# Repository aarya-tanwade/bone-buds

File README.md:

# BoneBuds / OSSIS

We’re building OSSIS, the first BoneBuds prototype: a Bluetooth audio system that delivers sound through bone-conduction transducers.

We have verified Bluetooth playback, wireless firmware updates and independent left/right stereo playback. Our current bench prototype uses an ESP32-WROOM-32, two MAX98357A amplifiers and two separate bone-conduction transducers (BCTs).

The next stage is moving from breadboard testing towards a compact perfboard assembly, battery-powered operation and a wearable product design.

[Current firmware](code/ossis/main/main.ino) · [Upload guide](code/README.md) · [Bench setup](docs/test-setup.md) · [Test records](docs/test-results.md) · [Development log](docs/development-log.md)

## Current status

| Test | Scope | Status |
| --- | --- | --- |
| **T01: Bluetooth A2DP playback** | Bluetooth audio reception, DSP and I²S amplification | **PASSED** · 24 October 2026 |
| **T02: Wireless OTA** | Firmware uploads over Wi-Fi using ArduinoOTA | **PASSED** · 29 October 2026 |
| **T03: Independent stereo** | Two MAX98357A amplifiers and two separate BCTs | **PASSED** |

## Audio architecture

The ESP32 receives Bluetooth Classic A2DP audio in two digital channels. Each channel passes through its own independent DSP processing chain before reaching the stereo I²S output.

Both MAX98357A amplifiers receive the shared I²S clock and data connections. Their SD_MODE configurations select different channels, allowing each amplifier to drive its own transducer.

```mermaid
flowchart TD
    phone["Phone / Bluetooth audio source"]
    bt["Bluetooth Classic A2DP"]
    esp["ESP32-WROOM-32"]

    phone --> bt
    bt --> esp

    esp --> dsp["Stereo DSP<br/>32-bit floating-point processing"]

    dsp --> left["Left DSP chain"]
    dsp --> right["Right DSP chain"]

    left --> i2s["Stereo I²S output<br/>44.1 kHz / 16-bit"]
    right --> i2s

    i2s --> bus["Shared BCLK / WS / DIN"]

    bus --> ampL["MAX98357A<br/>Left channel selected"]
    bus --> ampR["MAX98357A<br/>Right channel selected"]

    ampL --> bctL["Left BCT"]
    ampR --> bctR["Right BCT"]

    classDef source fill:#edf3f6,stroke:#7896a8,color:#17324b
    classDef processing fill:#eaf2f8,stroke:#6c91ad,color:#17324b
    classDef hardware fill:#f5f1e9,stroke:#b29b70,color:#42351e
    classDef output fill:#edf4ed,stroke:#83a286,color:#23442a

    class phone,bt source
    class esp,dsp,left,right,i2s,bus processing
    class ampL,ampR hardware
    class bctL,bctR output
```

### DSP configuration

The current stereo firmware uses separate `BoneChannelDSP` instances for left and right audio processing.

| DSP stage | Configured setting | Purpose |
| --- | --- | --- |
| Pre-gain | -4.5 dB | Creates headroom before EQ boosts |
| High-pass | 180 Hz, Q = 0.7071 | Attenuates low-frequency content |
| Peaking EQ | 2.8 kHz, +4 dB, 0.8-octave bandwidth | Emphasizes the presence region |
| High shelf | 5.5 kHz, +2.5 dB, slope = 1.0 | Adjusts high-frequency balance |
| Output limiter | Soft-knee above 90% full scale | Reduces harsh peak clipping |
| Master volume | 1.0 | Output scaling |

The DSP chain uses 32-bit floating-point calculations, followed by a soft-knee limiter and a signed 16-bit safety clamp.

The configured I²S format is **44.1 kHz, 16-bit, two channels**. Hardware APLL is enabled in the current firmware.

[Current DSP implementation](code/ossis/main/main.ino) · [T03 test documentation](code/ossis/tests/T03_independent_stereo/README.md)

## T01: Bluetooth A2DP playback

**PASSED · 24 October 2026.** We verified Bluetooth Classic A2DP streaming through the ESP32-WROOM-32, MAX98357A and one bone-conduction transducer.

[Verified T01 sketch](code/ossis/tests/T01_wroom_bt_a2dp/T01_wroom_bt_a2dp.ino) · [Reproduce the test](code/ossis/tests/T01_wroom_bt_a2dp/README.md) · [Bench wiring](docs/test-setup.md)

### 29 October: Shared-amplifier playback

We subsequently tested two Adafruit 8 Ω, 1 W BCTs connected in parallel to one MAX98357A amplifier, using a phone as the Bluetooth source.

Audio was clear and loud at the contact points just in front of each ear, while surrounding sounds remained audible. Maximum volume was unnecessary.

There was no noticeable sound leakage at normal listening volume and only very faint leakage at maximum volume when listening closely.

Laptop streaming produced slight noise and intermittent breakup, so we selected a phone as our reference source for subsequent testing.

[Recorded observations](docs/test-results.md#t01-bluetooth-a2dp-playback)

## T02: Wireless OTA

**PASSED · 29 October 2026.** We verified wireless firmware uploads on the ESP32-WROOM-32 using ArduinoOTA over Wi-Fi.

OTA allows us to upload firmware through Arduino IDE without a USB data connection after the initial USB installation.

Bluetooth playback and OTA operate on separate boots. The firmware saves the operating mode using Preferences before restarting.

### Operating modes

```mermaid
flowchart TD
    boot{"Boot: saved operating mode?"}

    boot -->|Bluetooth or unset| bt["Bluetooth mode<br/>Wi-Fi off"]
    boot -->|OTA| ota["Wi-Fi access point<br/>ArduinoOTA active"]

    bt -->|Connected within 20 s| play["Bluetooth audio playback"]
    bt -->|No initial connection| save["Save OTA mode / restart"]

    play -->|Connection lost for 3 s| save

    save --> ota

    ota --> upload["Wireless firmware upload<br/>Port 3232"]
    upload -->|Upload error| ota
    upload -->|Upload complete| restart["Save Bluetooth mode / restart"]

    ota -->|Start Bluetooth button| restart
    restart --> boot
```

- **Bluetooth mode:** Pair within the initial 20-second connection window. Once connected, audio mode remains active.
- **Disconnection:** Losing an established Bluetooth connection for 3 seconds triggers OTA mode. Pausing music while still connected does not.
- **OTA mode:** The ESP32 runs a Wi-Fi access point and ArduinoOTA on port 3232. There is no automatic OTA timeout.
- **Return to playback:** A completed firmware update saves Bluetooth mode for the next boot.
- **Manual return:** The **Start Bluetooth** button at `http://192.168.4.1` saves Bluetooth mode and restarts the board.

<details>
<summary>Detailed OTA procedure and operating notes</summary>

1. Install the firmware over USB initially.
2. Leave Bluetooth unconnected for 20 seconds, or disconnect an established connection and wait 3 seconds.
3. Connect your computer to the ESP32 Wi-Fi access point.
4. Open `http://192.168.4.1` to check OTA mode.
5. Select the ESP32 network port in Arduino IDE and upload the firmware.
6. Wait for the update to complete and the board to restart.
7. Reconnect to the Bluetooth audio device.

The web page controls the operating mode; it is not a firmware upload form.

The saved mode survives a reset. A reset alone does not exit OTA mode.

</details>

| Demonstration | Arduino IDE record |
| :---: | :---: |
|  |  |
| Wireless firmware update | **OTA upload in progress** |

[T02 sketch](code/ossis/tests/T02_mono_ota/T02_mono_ota.ino) · [Mode flowchart and upload procedure](code/ossis/tests/T02_mono_ota/README.md) · [Test record](docs/test-results.md#t02-wireless-ota)

## T03: Independent Stereo Playback

**PASSED.** We successfully verified independent left and right audio playback using two MAX98357A amplifier modules and two separate bone-conduction transducers.

Each amplifier receives the same I²S clock and data signals but selects a different digital channel through its SD_MODE configuration.

The left amplifier drives the left BCT, and the right amplifier drives the right BCT.

### Hardware architecture

```mermaid
flowchart LR
    esp["ESP32-WROOM-32"]

    esp --> bus["Shared I²S bus<br/>GPIO 26 / 25 / 22"]

    bus --> left["Left MAX98357A"]
    bus --> right["Right MAX98357A"]

    left --> bctL["Left BCT"]
    right --> bctR["Right BCT"]
```

### Channel selection

The two amplifiers use different SD_MODE configurations:

| Amplifier | SD_MODE connection | Selected channel |
| --- | --- | --- |
| Left | Direct +5V connection | Left |
| Right | 1 kΩ / 230 Ω resistor divider | Right |

The tested right-channel resistor arrangement uses:

- 1 kΩ (Brown - Black - Red - Gold) from +5V to SD_MODE.
- 230 Ω (Red - Orange - Brown - Gold) from SD_MODE to GND.

> [!WARNING]
> Keep the speaker outputs of the two MAX98357A amplifiers electrically separate. Each amplifier drives only its own BCT.

### Hardware evidence

The photograph below documents our actual T03 stereo bench configuration.

*OSSIS T03: Independent left and right audio playback using two amplifier modules.*

### Verification results

| Check | Result |
| --- | --- |
| Bluetooth A2DP connection | **PASSED** |
| Left-channel playback | **PASSED** |
| Right-channel playback | **PASSED** |
| Independent left/right output | **PASSED** |
| Both amplifiers operating together | **PASSED** |
| Separate BCT outputs | **PASSED** |

We verified independent channel playback using stereo test audio.

[T03 test sketch](code/ossis/tests/T03_independent_stereo/T03_independent_stereo.ino) · [T03 test procedure](code/ossis/tests/T03_independent_stereo/README.md) · [T03 test record](docs/test-results.md#t03-independent-stereo-playback)

## Bill of Materials

Our current T03 bench prototype uses one ESP32 development board, two amplifier modules and two bone-conduction transducers.

| Reference photo | Part and use | Qty | Unit cost | Total |
| :---: | --- | :---: | ---: | ---: |
|  | [ESP32-WROOM-32 development board](https://docs.espressif.com/projects/esp-idf/en/v4.4/esp32/hw-reference/esp32/get-started-devkitc.html)<br>38 pins; Bluetooth, DSP, I²S and Wi-Fi | 1 | ₹400 | ₹400 |
|  | [MAX98357A amplifier](https://www.hubtronics.in/max98357a-stereo-amplifier-module)<br>I²S input, mono Class-D output | 2 | ₹200 | ₹400 |
|  | [Adafruit BCT, product 1674](https://www.adafruit.com/product/1674)<br>8 Ω, 1 W RMS each | 2 | ₹700 | ₹1,400 |
| | **Estimated hardware total** | | | **₹2,200** |

The 1 kΩ and 230 Ω resistors used for right-channel selection are existing components and are not included in the estimated total.

### Wiring

The current bench wiring uses shared I²S connections and independent amplifier outputs.

[Connection table and SD_MODE wiring](docs/test-setup.md)

[Physical T03 hardware setup](images/tests/T03/t03-stereo-hardware-setup.jpg)

The older [shared-amplifier wiring diagram](images/diagrams/ossis-wiring.svg) documents the earlier two-BCT mono configuration, not the current independent stereo setup. The original [T01 wiring diagram](images/diagrams/t01-wiring.svg) is retained as a historical reference.

## Firmware and repository

> [!IMPORTANT]
> **Current firmware:** [main.ino](code/ossis/main/main.ino) contains the latest working **T03 independent stereo implementation**. It currently does not include the T02 wireless OTA functionality.

```text
code/
  README.md
  ossis/
    main/
      main.ino                       Current T03 stereo firmware
    tests/
      T01_wroom_bt_a2dp/
        T01_wroom_bt_a2dp.ino        Bluetooth playback baseline
        README.md
      T02_mono_ota/
        T02_mono_ota.ino             Wireless OTA experiment
        README.md
      T03_independent_stereo/
        T03_independent_stereo.ino   Independent stereo test
        README.md

docs/
  README.md                          Documentation index
  test-setup.md                      Current hardware connections
  test-results.md                    Verified test records
  development-log.md                 Engineering history

images/
  hero/                              Project masthead
  components/                        Hardware reference photos
  diagrams/                          Architecture and wiring diagrams
  tests/
    T02/                             OTA test evidence
    T03/                             Stereo hardware evidence
```

[Documentation index](docs/README.md) · [Test results](docs/test-results.md) · [Development log](docs/development-log.md) · [Firmware guide](code/README.md)

## Next work

With independent stereo playback verified, our next objective is to move towards a more compact, battery-powered and wearable prototype.

| Work | State | Next action |
| --- | --- | --- |
| **Perfboard prototype** | NEXT | Replace temporary breadboard connections with a more stable assembly |
| **Battery integration** | Planned | Develop portable power and test battery-powered playback and runtime |
| **Product concept** | Planned | Explore product form, wearable arrangement and industrial design ideas |
| **3D mechanical design** | Not started | Develop the enclosure and mechanical assembly |
| **Final testing** | Planned | Validate audio quality, reliability, power consumption and thermal behaviour |
| **System optimization** | Planned | Refine firmware, hardware and overall listening experience |

[Development log](docs/development-log.md) · [Test results](docs/test-results.md) · [Bench setup](docs/test-setup.md)

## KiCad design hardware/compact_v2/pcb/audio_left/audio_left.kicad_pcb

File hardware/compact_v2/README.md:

# Bone Buds - Rev B | Compact custom-IC design

**Status:** Preliminary engineering design / Stage 2. Not fabrication-validated.

This is **one wearable hardware revision** composed of three PCB projects:

- **controller** - central SoC, power, charging and system interconnects.
- **audio_left** - left-side audio electronics.
- **audio_right** - right-side audio electronics.

## Contents

- `pcb/controller/`, `pcb/audio_left/`, `pcb/audio_right/`: editable KiCad schematic + board + project files.
- `pcb/BoneBuds.pretty/`, `pcb/BoneBuds.kicad_sym`, `pcb/models/`: custom library/model resources.
- `mechanical/`: CAD build scripts and real STEP/STL exports for the assembled wearable.
- `exports/`: schematic PDFs and design visualization images.
- `documentation/`: DRC/ERC reports, design data, CAD checks and other engineering notes.
- `tools/`: scripts used to generate or inspect the design.
- `sources/`: part datasheets / reference material.

## Engineering cautions

1. ERC/DRC reports are design-rule checks, **not electrical, RF or clinical qualification**.
2. Purchased component dimensions, microphone acoustic routing, battery safety,
   antenna performance, enclosure comfort and transducer contact require physical validation.
3. Before ordering PCBs: reopen all three designs in KiCad, review the actual
   ERC/DRC reports, verify parts and footprints, and regenerate manufacturing outputs.
4. Manufacturing exports are intentionally kept local until reviewed.
5. An empty `mechanical/fusion/` folder does not establish that a native Fusion design was made.
   The available STEP/STL and CAD scripts are the currently identified artifacts.

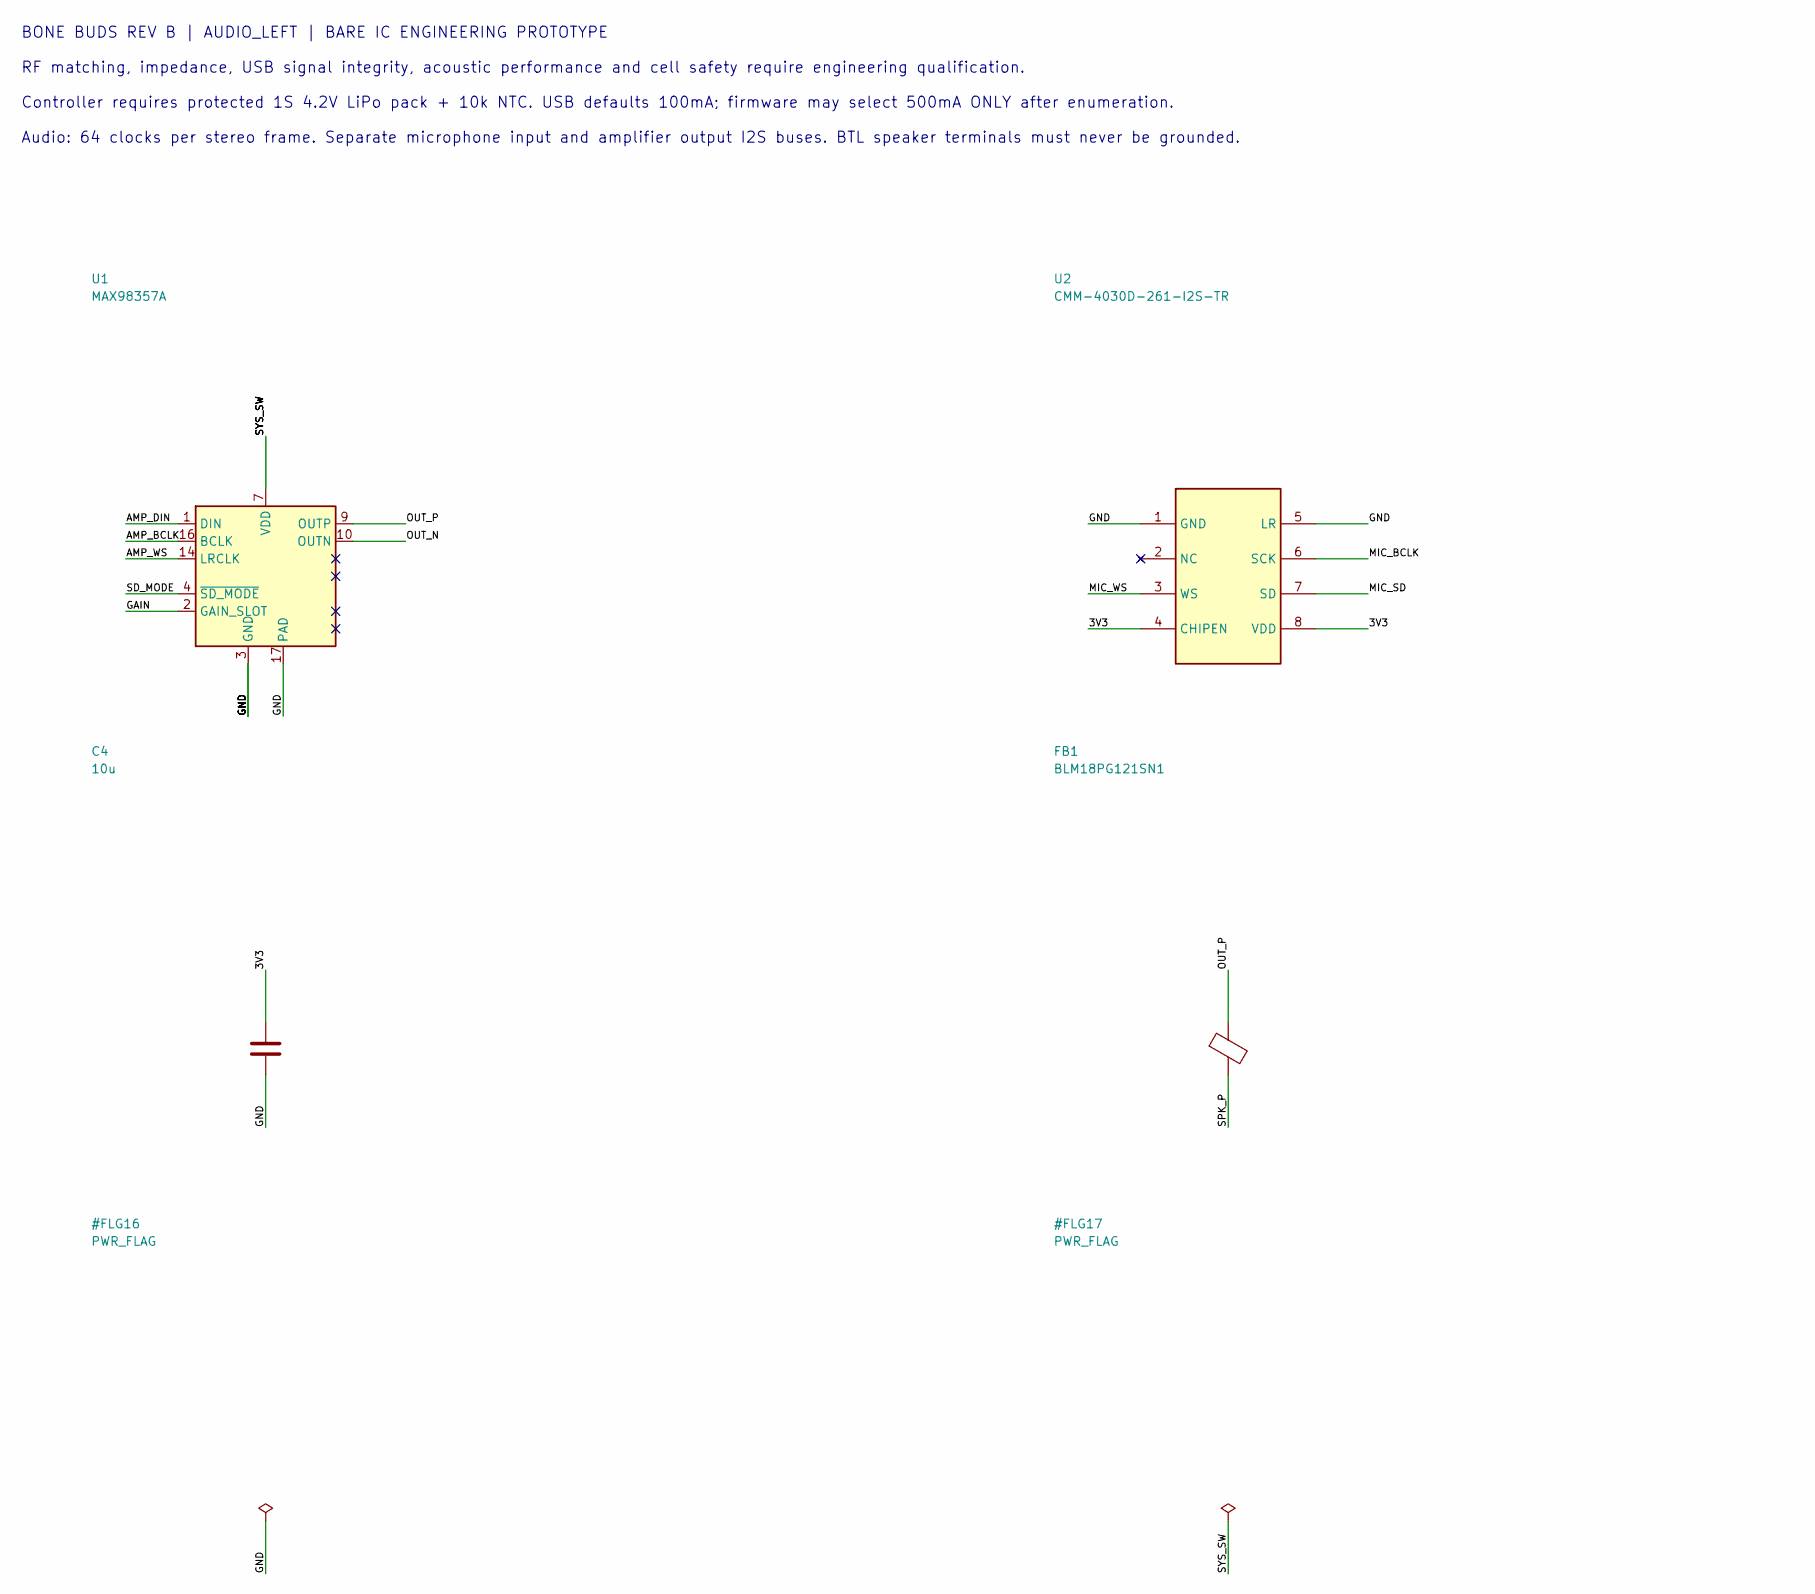
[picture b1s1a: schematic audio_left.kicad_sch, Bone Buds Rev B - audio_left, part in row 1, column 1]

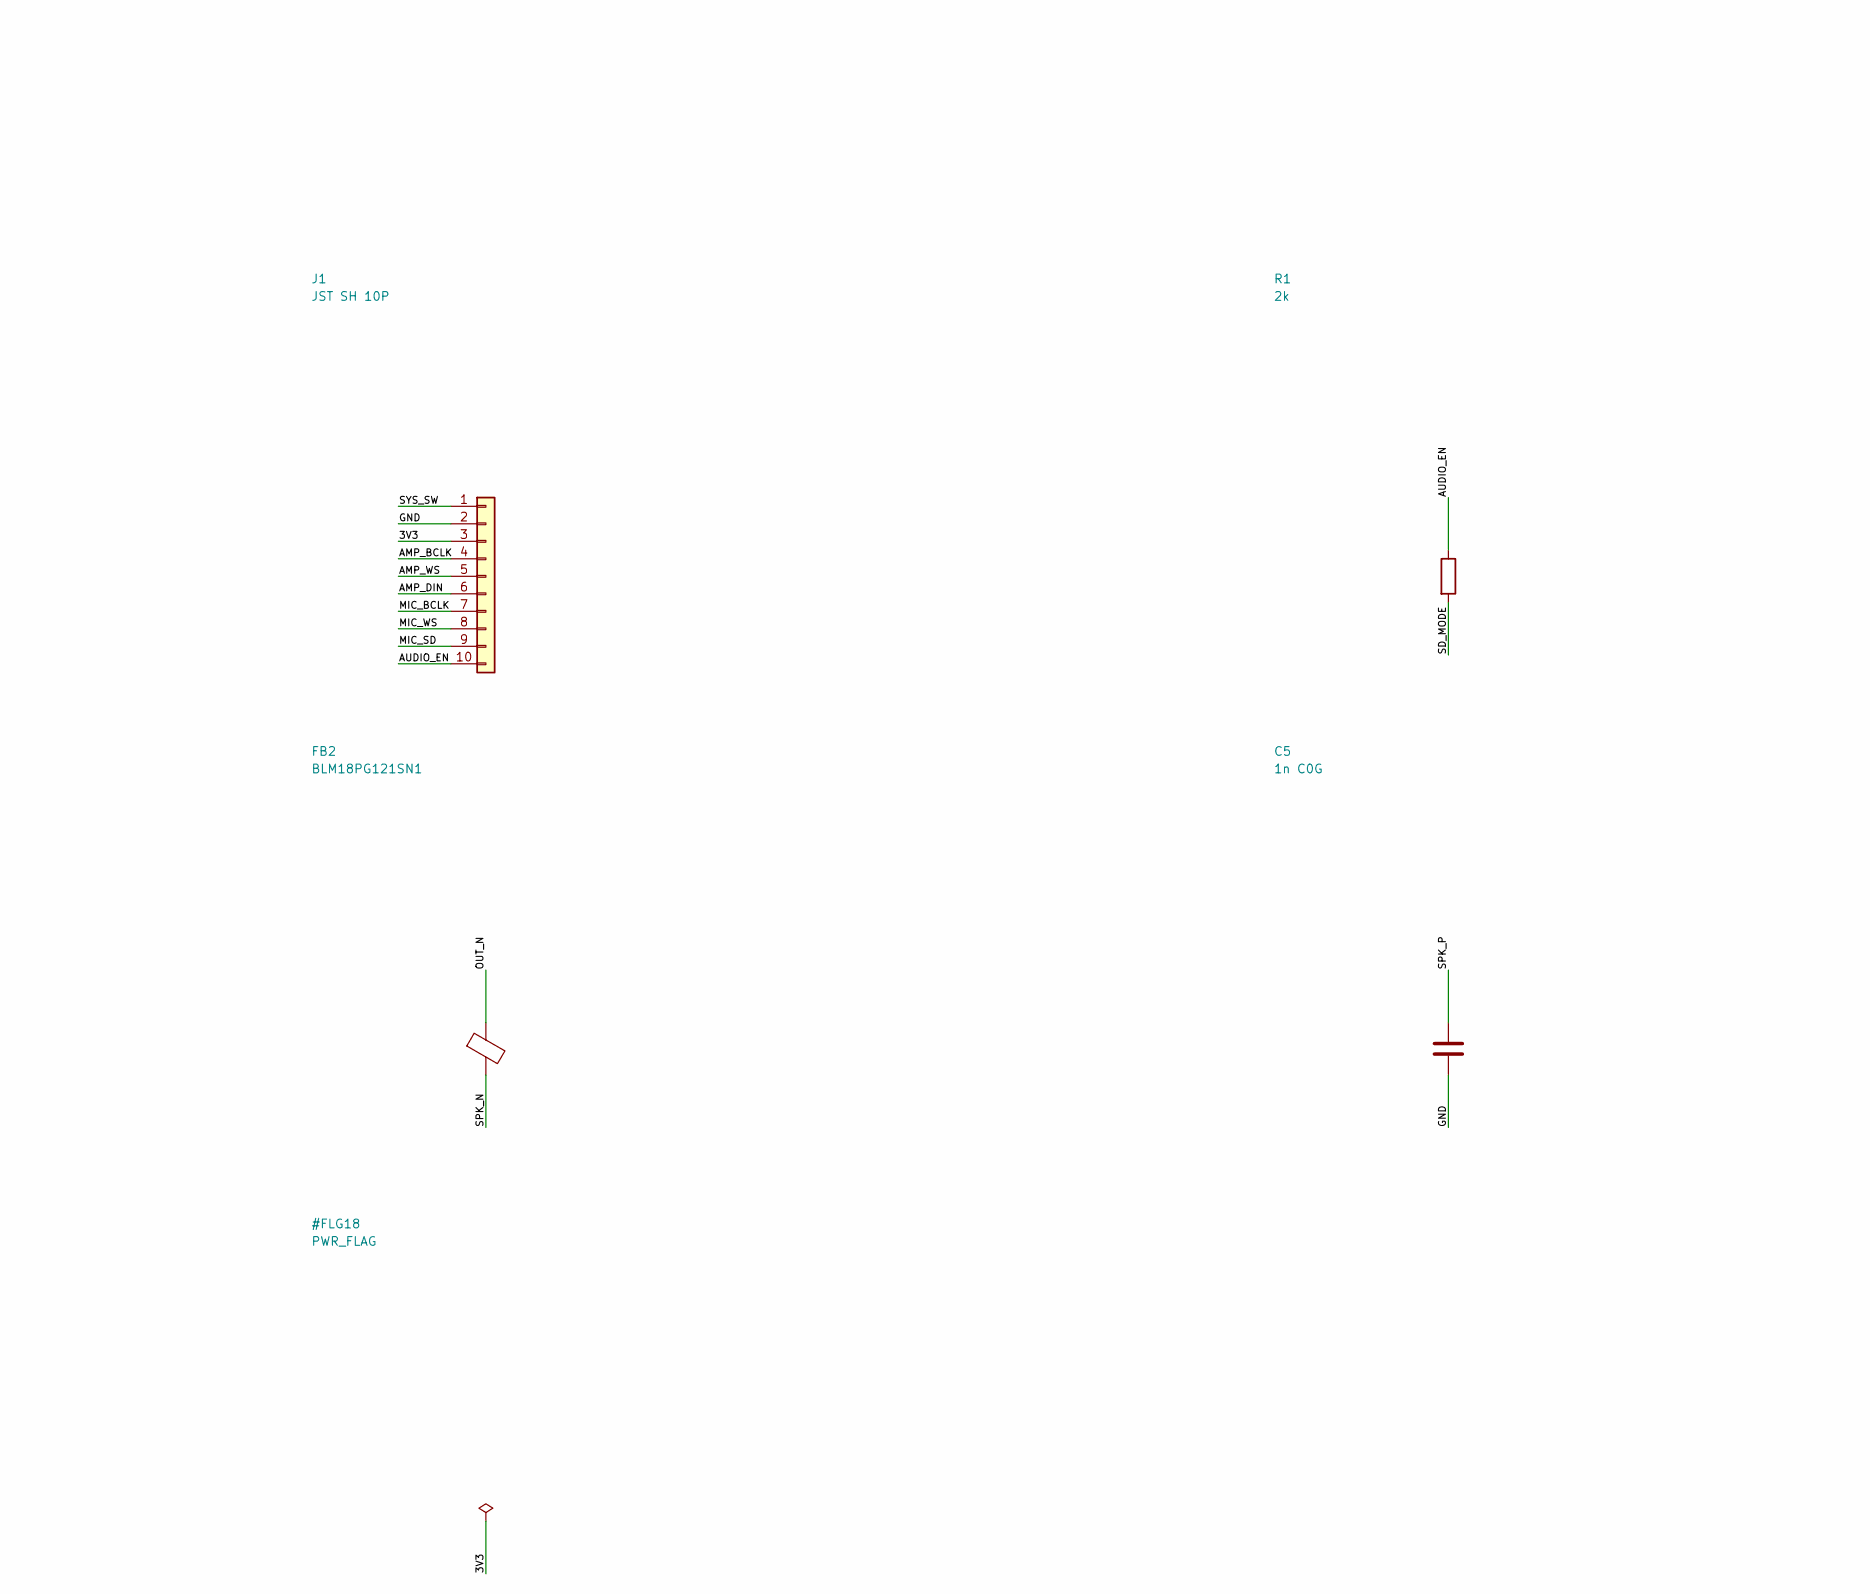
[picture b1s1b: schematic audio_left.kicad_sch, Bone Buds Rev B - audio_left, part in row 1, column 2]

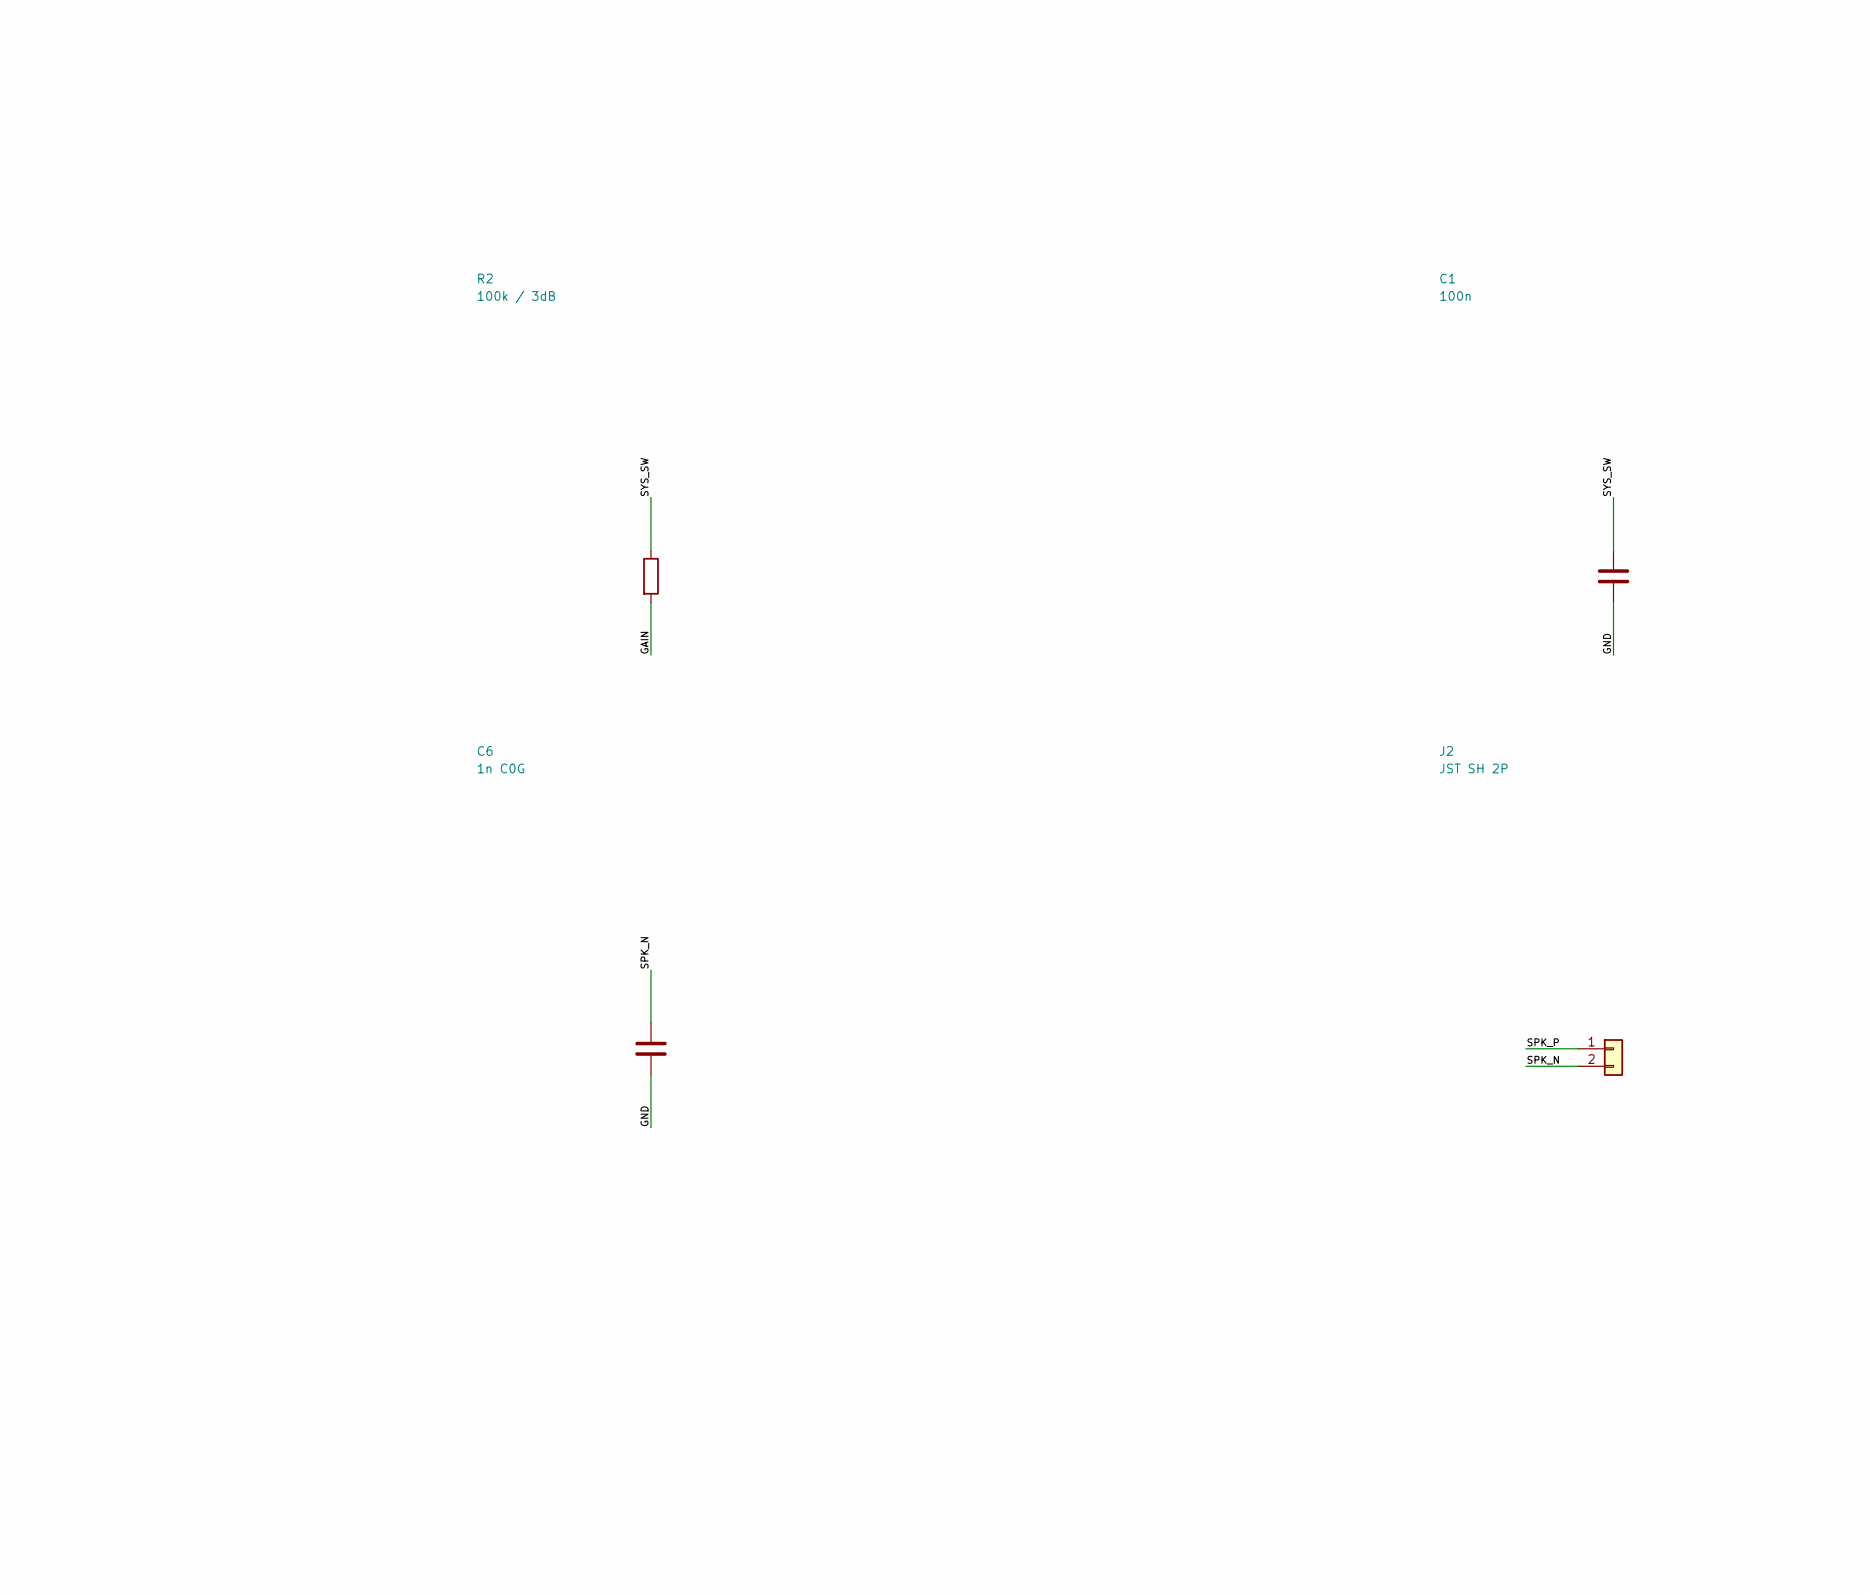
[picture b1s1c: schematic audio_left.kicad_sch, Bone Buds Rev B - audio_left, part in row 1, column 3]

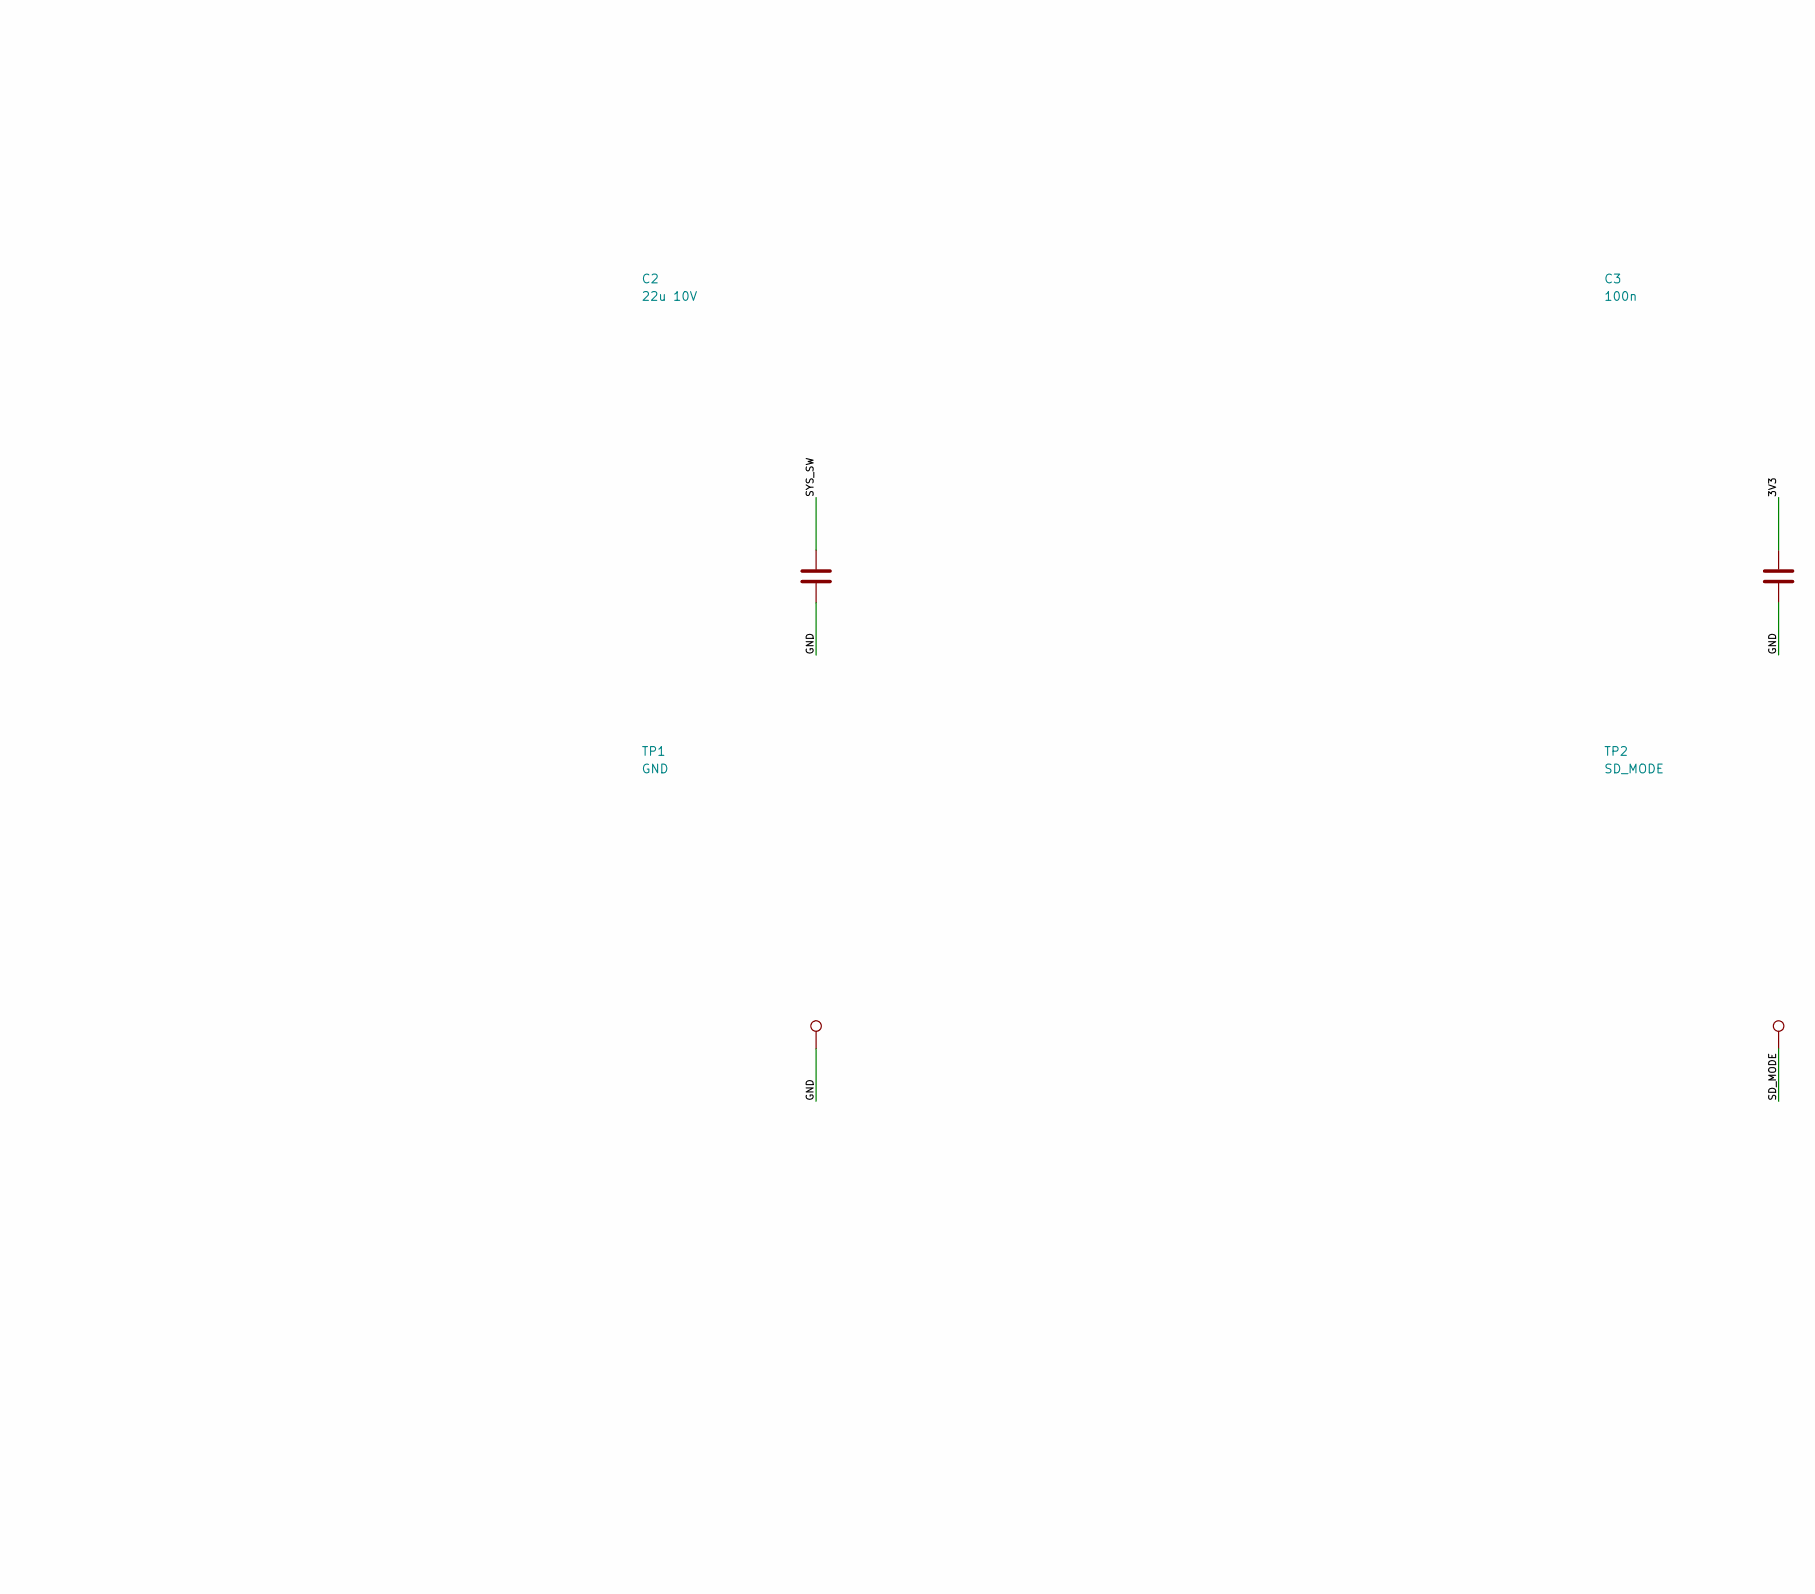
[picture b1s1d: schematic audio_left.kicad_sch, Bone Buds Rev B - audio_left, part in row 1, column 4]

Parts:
C1, C3: 100n; C_0402_1005Metric
C2: 22u 10V; C_0805_2012Metric
C4: 10u; C_0603_1608Metric
C5, C6: 1n C0G; C_0402_1005Metric
FB1, FB2: BLM18PG121SN1; L_0603_1608Metric
J1: JST SH 10P; JST_SH_BM10B-SRSS-TB_1x10-1MP_P1.00mm_Vertical
J2: JST SH 2P; JST_SH_BM02B-SRSS-TB_1x02-1MP_P1.00mm_Vertical
R1: 2k; R_0402_1005Metric
R2: 100k / 3dB; R_0402_1005Metric
TP1: GND; TestPoint_Pad_D1.0mm
TP2: SD_MODE; TestPoint_Pad_D1.0mm
U1: MAX98357A; TQFN-16-1EP_3x3mm_P0.5mm_EP1.23x1.23mm
U2: CMM-4030D-261-I2S-TR; CMM4030

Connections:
/3V3: C3.1, C4.1, J1.3, U2.4 (CHIPEN), U2.8 (VDD)
/AMP_BCLK: J1.4, U1.16 (BCLK)
/AMP_DIN: J1.6, U1.1 (DIN)
/AMP_WS: J1.5, U1.14 (LRCLK)
/AUDIO_EN: J1.10, R1.1
/GAIN: R2.2, U1.2 (GAIN_SLOT)
/GND: C1.2, C2.2, C3.2, C4.2, C5.2, C6.2, J1.2, TP1.1, U1.3 (GND), U1.11 (GND), U1.15 (GND), U1.17 (PAD), U2.1 (GND), U2.5 (LR)
/MIC_BCLK: J1.7, U2.6 (SCK)
/MIC_SD: J1.9, U2.7 (SD)
/MIC_WS: J1.8, U2.3 (WS)
/OUT_N: FB2.1, U1.10 (OUTN)
/OUT_P: FB1.1, U1.9 (OUTP)
/SD_MODE: R1.2, TP2.1, U1.4 (~SD_MODE)
/SPK_N: C6.1, FB2.2, J2.2
/SPK_P: C5.1, FB1.2, J2.1
/SYS_SW: C1.1, C2.1, J1.1, R2.1, U1.7 (VDD), U1.8 (VDD)

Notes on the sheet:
BONE BUDS REV B | AUDIO_LEFT | BARE IC ENGINEERING PROTOTYPE
RF matching, impedance, USB signal integrity, acoustic performance and cell safety require engineering qualification.
Controller requires protected 1S 4.2V LiPo pack + 10k NTC. USB defaults 100mA; firmware may select 500mA ONLY after enumeration.
Audio: 64 clocks per stereo frame. Separate microphone input and amplifier output I2S buses. BTL speaker terminals must never be grounded.

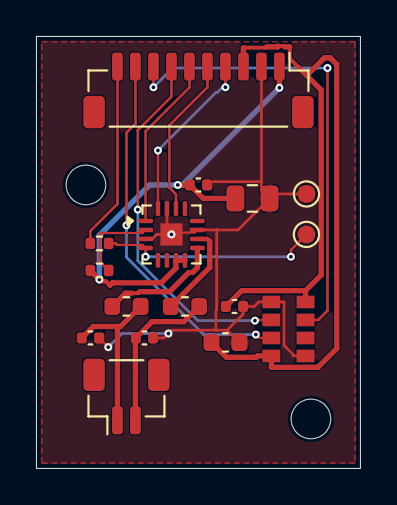
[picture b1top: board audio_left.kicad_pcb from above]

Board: 4 copper layers, 18.0 x 24.0 mm, 18 parts (0 on the bottom side), 16 nets.

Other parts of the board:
H1, H2: MountingHole_2.2mm_M2

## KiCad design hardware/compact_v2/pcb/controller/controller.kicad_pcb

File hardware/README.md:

# Bone Buds hardware

## Current design: Rev B (compact custom-IC wearable)

See [Rev B hardware](./compact_v2/README.md).

Rev B is a **design-stage**, multi-board architecture using a compact controller PCB and
left/right audio PCBs. The matching wearable CAD is in the mechanical directory.
These boards are **not claimed to be electrically bench-tested, RF-qualified,
medically validated, or production-certified**. Verify footprints, electrical
performance, physical fit, charging safety and acoustics before fabrication/use.

The original development-board carrier (Rev A/V1) has been retained in a local
backup outside this Git repository rather than deleted.

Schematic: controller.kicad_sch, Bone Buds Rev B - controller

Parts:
C1, C6, C7, C8, C9, C10, C21, C24: 100n; C_0402_1005Metric
C2, C5: 1u; C_0402_1005Metric
C3, C4: 12p C0G tune; C_0402_1005Metric
C11: 10u; C_0603_1608Metric
C12: 22u; C_0805_2012Metric
C13, C14: 1.5p RF tune; C_0402_1005Metric
C15, C16: 4.7u 10V; C_0603_1608Metric
C17: 10u 10V; C_0805_2012Metric
C18: 1n; C_0402_1005Metric
C19, C20, C22, C23: 10u; C_0805_2012Metric
D1: BAT54H; D_SOD-323
FB1: BLM18AG601SN1 600R; L_0603_1608Metric
J1: U.FL 2.4GHz antenna; U.FL_Hirose_U.FL-R-SMT-1_Vertical
J2: GCT USB4105-GF-A; USB_C_Receptacle_GCT_USB4105-xx-A_16P_TopMnt_Horizontal
J3: JST SH 3P; JST_SH_BM03B-SRSS-TB_1x03-1MP_P1.00mm_Vertical
J4, J5: JST SH 10P; JST_SH_BM10B-SRSS-TB_1x10-1MP_P1.00mm_Vertical
J6: JST SH 2P; JST_SH_BM02B-SRSS-TB_1x02-1MP_P1.00mm_Vertical
L1: 24nH RF tuning; L_0402_1005Metric
L2: 2.4nH RF tune; L_0402_1005Metric
L3: 1.5uH >=2A DCR<100m; L_Wuerth_MAPI-3015
R1, R14, R15, R16, R17, R18: 33R; R_0402_1005Metric
R2, R3, R21, R22, R23: 10k; R_0402_1005Metric
R4, R11, R19, R20: 100k; R_0402_1005Metric
R5, R6: 5.1k 1%; R_0402_1005Metric
R7, R8: 22R; R_0402_1005Metric
R9: 3.57k 1% 249mA; R_0402_1005Metric
R10: 3.48k 1%; R_0402_1005Metric
R12: 1M; R_0402_1005Metric
R13: 330k; R_0402_1005Metric
R24: 100R; R_0402_1005Metric
SW1: POWER; SW_SPDT_PCM12
SW2: MUTE / PLAY; SW_SPDT_PCM12
TP1: BOOT; TestPoint_Pad_D1.0mm
TP2: CHIP_EN; TestPoint_Pad_D1.0mm
TP3: GND; TestPoint_Pad_D1.0mm
TP4: UART_TX; TestPoint_Pad_D1.0mm
TP5: UART_RX; TestPoint_Pad_D1.0mm
TP6: BAT; TestPoint_Pad_D1.0mm
TP7: SYS; TestPoint_Pad_D1.0mm
TP8: 3V3; TestPoint_Pad_D1.0mm
TP9: CHG; TestPoint_Pad_D1.0mm
TP10: PGOOD; TestPoint_Pad_D1.0mm
U1: ESP32-S3R8; QFN-56-1EP_7x7mm_P0.4mm_EP4x4mm
U2: W25Q128JVPIQ / 16 MB; WSON-8-1EP_6x5mm_P1.27mm_EP3.4x4.3mm
U3: USBLC6-2SC6; SOT-23-6
U4: BQ24074RGT; VQFN-16-1EP_3x3mm_P0.5mm_EP1.6x1.6mm
U5: TPS22917DBV; SOT-23-6
U6: TPS63031DSK; WSON-10-1EP_2.5x2.5mm_P0.5mm_EP1.2x2mm
U7: TPS3839K33DBZR / 3.08V; SOT-23
Y1: 40MHz 10ppm CL8pF; Crystal_SMD_2016-4Pin_2.0x1.6mm

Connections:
/3V3: C7.1, C8.1, C12.1, C22.1, C23.1, FB1.1, J4.3, J5.3, R2.1, R3.1, R21.2, TP8.1, U1.20 (VDD3P3_RTC), U1.46 (VDD3P3_CPU), U6.1 (VOUT), U6.10 (FB), U7.3 (VDD)
/3V3_RF: C6.1, C9.1, C11.1, FB1.2, U1.2 (VDD3P3), U1.3 (VDD3P3), U1.55 (VDDA), U1.56 (VDDA)
/AMP_BCLK: J4.4, J5.4, R14.2
/AMP_BCLK_SRC: R14.1, U1.9 (GPIO4)
/AMP_DIN: J4.6, J5.6, R16.2
/AMP_DIN_SRC: R16.1, U1.11 (GPIO6)
/AMP_WS: J4.5, J5.5, R15.2
/AMP_WS_SRC: R15.1, U1.10 (GPIO5)
/AUDIO_EN: J4.10, J5.10, SW2.2 (B)
/AUDIO_GPIO: R20.1, SW2.1 (A), U1.15 (GPIO10)
/BAT: C16.1, J3.1, R12.1, TP6.1, U4.2 (BAT), U4.3 (BAT)
/BAT_ADC: C24.1, R12.2, R13.1, U1.6 (GPIO1)
/BAT_NTC: J3.3, U4.1 (TS)
/BOOT: R3.2, TP1.1, U1.5 (GPIO0)
/BUCK_L1: L3.1, U6.4 (L1)
/BUCK_L2: L3.2, U6.2 (L2)
/CC1: J2.A5 (CC1), R5.1
/CC2: J2.B5 (CC2), R6.1
/CHG: TP9.1, U4.9 (~CHG)
/CHIP_EN: C5.1, D1.2 (A), R2.2, TP2.1, U1.4 (CHIP_PU)
/CT: C18.1, U5.4 (CT)
/DN_ESD: J2.A7 (D-), J2.B7 (D-), R8.1, U3.3 (I/O2), U3.4 (I/O2)
/DP_ESD: J2.A6 (D+), J2.B6 (D+), R7.1, U3.1 (I/O1), U3.6 (I/O1)
/GND: C1.2, C2.2, C3.2, C4.2, C5.2, C6.2, C7.2, C8.2, C9.2, C10.2, C11.2, C12.2, C13.2, C14.2, C15.2, C16.2, C17.2, C18.2, C19.2, C20.2, C21.2, C22.2, C23.2, C24.2, J1.2 (Ext), J2.A1 (GND), J2.A12 (GND), J2.B1 (GND), J2.B12 (GND), J2.SH (SHIELD), J3.2, J4.2, J5.2, J6.2, R4.2, R5.2, R6.2, R9.2, R10.2, R11.2, R13.2, R19.2, R20.2, R22.2, R23.2, SW1.3 (C), SW2.3 (C), TP3.1, U1.57 (GND), U2.4 (GND), U2.9 (EP), U3.2 (GND), U4.4 (~CE), U4.5 (EN2), U4.8 (VSS), U4.17 (VSS), U5.2 (GND), U6.3 (PGND), U6.9 (GND), U6.11 (PGND), U7.1 (GND), Y1.2 (G), Y1.4 (G)
/ILIM: R10.1, U4.12 (ILIM)
/ISET: R9.1, U4.16 (ISET)
/MIC_BCLK: J4.7, J5.7, R17.2
/MIC_BCLK_SRC: R17.1, U1.12 (GPIO7)
/MIC_SD: J4.9, J5.9, R19.1, U1.14 (GPIO9)
/MIC_WS: J4.8, J5.8, R18.2
/MIC_WS_SRC: R18.1, U1.13 (GPIO8)
/PGOOD: TP10.1, U4.7 (~PGOOD)
/PWR_ON: R11.1, SW1.2 (B), U5.3 (ON)
/QOD: R24.1, U5.5 (QOD)
/RESET_SUP: D1.1 (K), U7.2 (~RESET)
/RF_50: C14.1, J1.1 (In), L2.2
/RF_CHIP: C13.1, L2.1, U1.1 (LNA_IN)
/SPI_CLK: R1.1, U1.33 (SPICLK)
/SPI_CLK_FLASH: R1.2, U2.6 (CLK)
/SPI_CS: U1.32 (SPICS0), U2.1 (~CS)
/SPI_D: U1.35 (SPID), U2.5 (DI/IO_{0})
/SPI_HD: U1.30 (SPIHD), U2.7 (~HOLD/~RESET/IO_{3})
/SPI_Q: U1.34 (SPIQ), U2.2 (DO/IO_{1})
/SPI_WP: U1.31 (SPIWP), U2.3 (~WP/IO_{2})
/STRAP45: R22.1, U1.51 (GPIO45)
/STRAP46: R23.1, U1.52 (GPIO46)
/SYS: C17.1, SW1.1 (A), TP7.1, U4.10 (OUT), U4.11 (OUT), U5.1 (VIN)
/SYS_SW: C19.1, C20.1, C21.1, J4.1, J5.1, R24.2, U5.6 (VOUT), U6.5 (VIN), U6.6 (EN), U6.7 (PS/SYNC), U6.8 (VINA)
/UART_RX: TP5.1, U1.50 (U0RXD)
/UART_TX: TP4.1, U1.49 (U0TXD)
/USB_500_EN: R4.1, U1.16 (GPIO11), U4.6 (EN1)
/USB_DN: R8.2, U1.25 (GPIO19/USB_D-)
/USB_DP: R7.2, U1.26 (GPIO20/USB_D+)
/USER_KEY: J6.1, R21.1, U1.17 (GPIO12)
/VBUS: C15.1, J2.A4 (VBUS), J2.A9 (VBUS), J2.B4 (VBUS), J2.B9 (VBUS), U3.5 (VBUS), U4.13 (IN)
/VDD_SPI: C1.1, C2.1, C10.1, U1.29 (VDD_SPI), U2.8 (VCC)
/XTAL_DRIVE: C3.1, L1.2, Y1.1
/XTAL_N: C4.1, U1.53 (XTAL_N), Y1.3
/XTAL_P: L1.1, U1.54 (XTAL_P)

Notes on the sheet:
BONE BUDS REV B | CONTROLLER | BARE IC ENGINEERING PROTOTYPE
RF matching, impedance, USB signal integrity, acoustic performance and cell safety require engineering qualification.
Controller requires protected 1S 4.2V LiPo pack + 10k NTC. USB defaults 100mA; firmware may select 500mA ONLY after enumeration.
Audio: 64 clocks per stereo frame. Separate microphone input and amplifier output I2S buses. BTL speaker terminals must never be grounded.

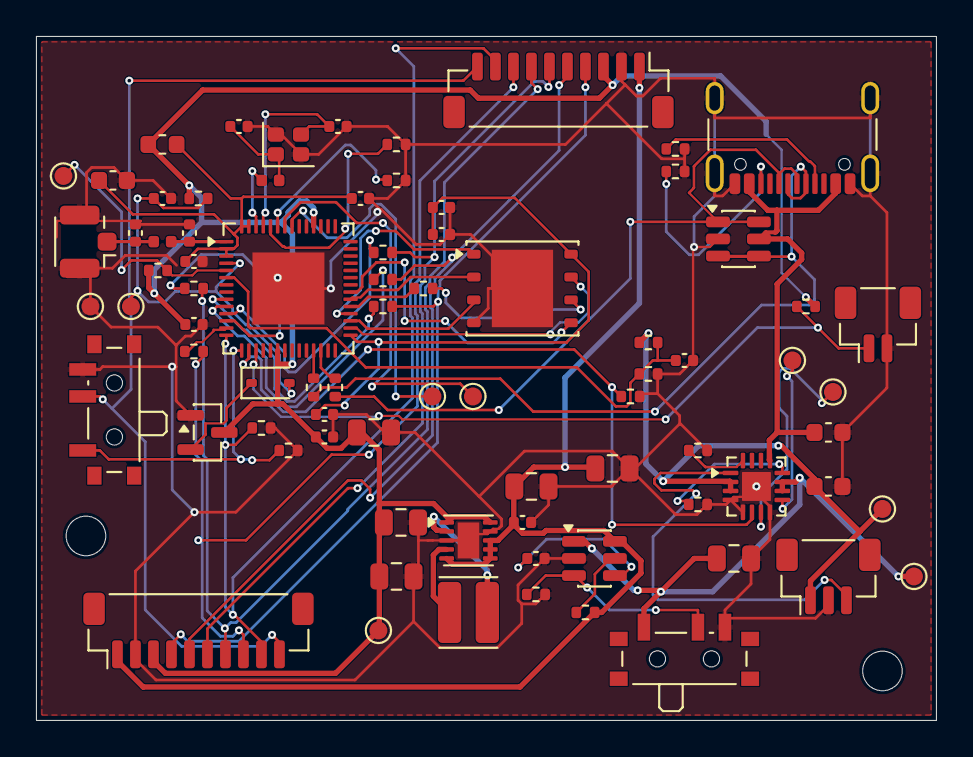
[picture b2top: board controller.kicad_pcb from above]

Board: 4 copper layers, 50.0 x 38.0 mm, 81 parts (0 on the bottom side), 59 nets.

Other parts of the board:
H1, H2: MountingHole_2.2mm_M2

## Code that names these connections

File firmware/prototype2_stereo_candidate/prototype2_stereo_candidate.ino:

// Bone Buds Rev A stereo bring-up candidate. NOT compiled or hardware-tested.
// Requires Arduino-ESP32 ESP_I2S.h, as used by the preserved Prototype 1 sketch.
// First use dummy loads. Verify SD_MODE voltages before connecting transducers.
#include <Arduino.h>
#include <ESP_I2S.h>

constexpr int MIC_BCLK=7, MIC_WS=8, MIC_SD=9;
constexpr int AMP_BCLK=4, AMP_WS=5, AMP_DOUT=6, AUDIO_EN=10;
constexpr int SAMPLE_RATE=16000;
constexpr int32_t PCM_LIMIT=4096; // Conservative bring-up ceiling, not a calibrated SPL limit.
I2SClass MicI2S, AmpI2S;
int32_t micBuffer[256];
int16_t audioBuffer[256];
bool enabled=false;
float gain=0.05f;

void mute() { digitalWrite(AUDIO_EN,LOW); enabled=false; }
void setup() {
  digitalWrite(AUDIO_EN,LOW); pinMode(AUDIO_EN,OUTPUT);
  Serial.begin(115200);
  MicI2S.setPins(MIC_BCLK,MIC_WS,-1,MIC_SD);
  AmpI2S.setPins(AMP_BCLK,AMP_WS,AMP_DOUT,-1);
  bool rx=MicI2S.begin(I2S_MODE_STD,SAMPLE_RATE,I2S_DATA_BIT_WIDTH_32BIT,I2S_SLOT_MODE_STEREO);
  bool tx=AmpI2S.begin(I2S_MODE_STD,SAMPLE_RATE,I2S_DATA_BIT_WIDTH_16BIT,I2S_SLOT_MODE_STEREO);
  if (!rx || !tx) { mute(); Serial.println("I2S init failed; MUTED"); while(true) delay(1000); }
  memset(audioBuffer,0,sizeof(audioBuffer));
  AmpI2S.write((uint8_t*)audioBuffer,sizeof(audioBuffer));
  Serial.println("Stereo ready, muted. e=enable; m=mute; +/-=small gain step (0..0.1).");
}
void loop() {
  if (Serial.available()) {
    char c=Serial.read();
    if(c=='m') mute();
    if(c=='e') {enabled=true; digitalWrite(AUDIO_EN,HIGH);}
    if(c=='+') gain=min(0.10f,gain+0.005f);
    if(c=='-') gain=max(0.0f,gain-0.005f);
  }
  size_t bytes=MicI2S.readBytes((char*)micBuffer,sizeof(micBuffer));
  if(bytes==0 || bytes%8!=0) { mute(); return; }
  size_t samples=bytes/sizeof(int32_t);
  for(size_t i=0;i<samples;i++) { // Keep BOTH L,R samples; Prototype 1 discarded R.
    int32_t pcm=(int32_t)((micBuffer[i]>>16)*gain);
    pcm=max(-PCM_LIMIT,min(PCM_LIMIT,pcm));
    audioBuffer[i]=enabled ? (int16_t)pcm : 0;
  }
  size_t expected=samples*sizeof(int16_t);
  if(AmpI2S.write((uint8_t*)audioBuffer,expected)!=expected) mute();
}

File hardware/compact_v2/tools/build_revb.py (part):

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    ic('U2','Memory_Flash:W25Q128JVP',{1:'SPI_CS',2:'SPI_Q',3:'SPI_WP',4:'GND',5:'SPI_D',6:'SPI_CLK_FLASH',7:'SPI_HD',8:'VDD_SPI',9:'GND'},(77,64),'W25Q128JVPIQ / 16 MB')
    r('R1','33R','SPI_CLK','SPI_CLK_FLASH',(71.5,64));c('C1','100n','VDD_SPI',(72.5,61));c('C2','1u','VDD_SPI',(72.5,59.5))
    add('Y1','40MHz 10ppm CL8pF','Device:Crystal_GND24','Crystal:Crystal_SMD_2016-4Pin_2.0x1.6mm',{1:'XTAL_DRIVE',2:'GND',3:'XTAL_N',4:'GND'},(64,56))
    add('L1','24nH RF tuning','Device:L','Inductor_SMD:L_0402_1005Metric',['XTAL_P','XTAL_DRIVE'],(63,58))
    c('C3','12p C0G tune','XTAL_DRIVE',(62,55));c('C4','12p C0G tune','XTAL_N',(66,55))
    r('R2','10k','3V3','CHIP_EN',(59,59));c('C5','1u','CHIP_EN',(57,59))
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    add('D1','BAT54H','Device:D_Schottky','Diode_SMD:D_SOD-323',{1:'RESET_SUP',2:'CHIP_EN'},(59,69))
    r('R12','1M','BAT','BAT_ADC',(84,67));r('R13','330k','BAT_ADC','GND',(84,69));c('C24','100n','BAT_ADC',(86,68))
    for i,(a,b,xy) in enumerate([('AMP_BCLK_SRC','AMP_BCLK',(68,65)),('AMP_WS_SRC','AMP_WS',(68,63.5)),('AMP_DIN_SRC','AMP_DIN',(68,62)),('MIC_BCLK_SRC','MIC_BCLK',(59,64)),('MIC_WS_SRC','MIC_WS',(59,67.5))],14):r('R'+str(i),'33R',a,b,xy)
    r('R19','100k','MIC_SD','GND',(62,72));r('R20','100k','AUDIO_GPIO','GND',(64,73))
    add('SW2','MUTE / PLAY','Switch:SW_SPDT','Button_Switch_SMD:SW_SPDT_PCM12',{1:'AUDIO_GPIO',2:'AUDIO_EN',3:'GND'},(54,74),90)
    conn('J4',bus,(59,83));conn('J5',bus,(79,53),180)
    conn('J6',['USER_KEY','GND'],(97,66));r('R21','10k','USER_KEY','3V3',(94,65))
    tp('TP8','3V3',(69,83));tp('TP9','CHG',(92,68));tp('TP10','PGOOD',(94,68))
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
